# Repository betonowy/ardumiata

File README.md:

# Engine health monitoring for Mazda MX-5 NB1

Firmware for custom Arduino Nano powered device. Mainly for precise engine health monitoring on track days. Features:

- Invisible, non-invasive piggyback off of factory wiring harness if needed at all.
- Modifications are reversible.
- Cleanly integrates with car's interior. 16x2 green display can replace smoking ashtray on NB1. I made a "mounting bracket" for it with a matte painted piece of wood.
- Monitoring engine health and more:
    - (ECT) Coolant temperature - piggybacked and calibrated against factory sensor and ECU measurement circuit. May alternatively use temp gauge circuit, but you're on your own to deal with that.
    - (EOT) Oil temperatoure - from Ecumaster Temperature Sensor.
    - (EOP) Oil pressure - from Ecumaster Pressure Sensor.
    - (BAT) Battery voltage (from ignition).
- Alarm when any measurement exceeds safe limits so you know when to cooldown or make an emergency shutdown.
- If your ECT ever breaks, you will know.

## Important notes

- ECT approximation function might need to be recalibrated/curve fitted for any other car than mine, especially if any part of PCB design is altered. Measuring temperatures/ECT voltage at the back of the engine with device attached and compensating for measured voltages when fan switches on and off at 97C and 93C is good enough, especially if you just need a relative guide for how hot the engine is. If outside EU, check your regional specs specifically.
- Despite the efforts, cabin fan can offset measurements up to 4 degrees upwards when on and it can't be fixed, take that into account or don't turn it.
- ECT relay is required to ensure device does not affect ECU measurements when device is in an inconsistent state i.e. during reset, or engine startup.
- Cars with no AC have a very convenient rubber cap that can feed wires through passenger side firewall.

# Building project

- PCB project initially made in KiCad 8.
- Source compilled with `avr-gcc` toolchain with Arduino package. For guide check out `Arduino-CMake-NG` project. Initially developed on a Linux system.

Assuming basic KiCad and CMake knowledge, you should already know how to build the project.

## Project layout

- `.` - miscelaneous files and root `CMakeLists.txt`.
- `src` - Firmware source code.
- `kicad` - KiCad PCB project.

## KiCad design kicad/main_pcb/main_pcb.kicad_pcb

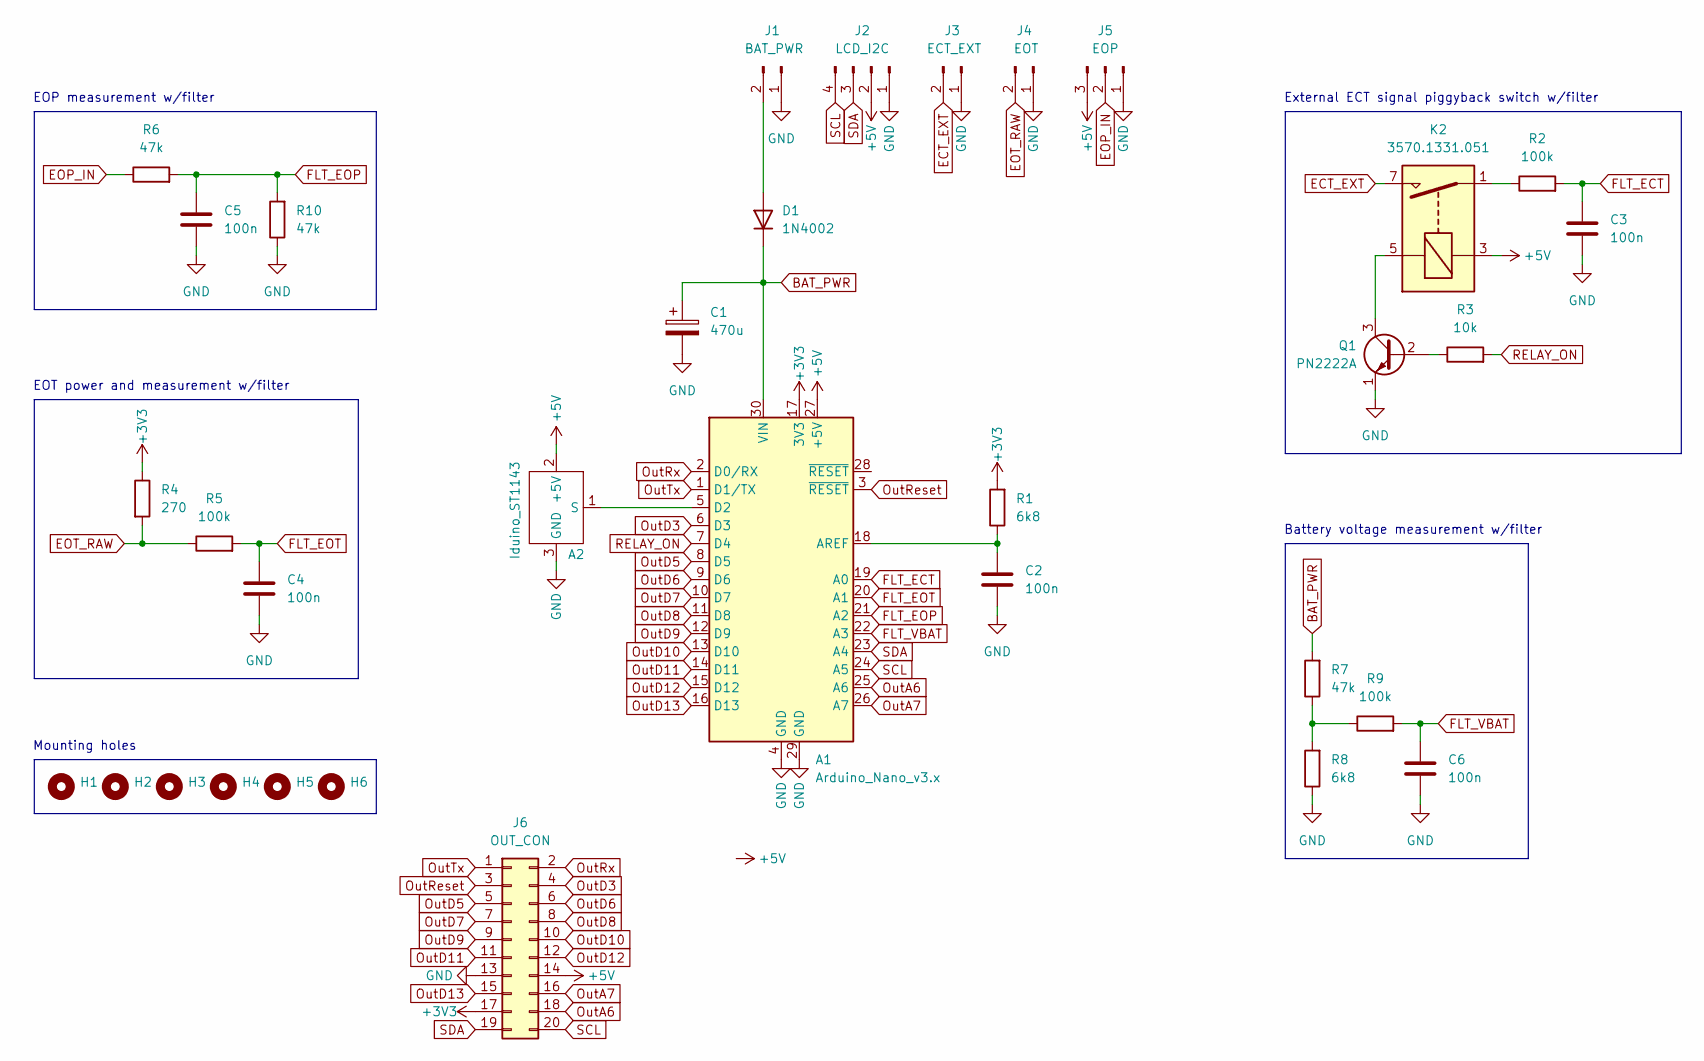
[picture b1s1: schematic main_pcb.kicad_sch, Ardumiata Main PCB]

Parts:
A1: Arduino_Nano_v3.x; Arduino_Nano
A2: Iduino_ST1143
C1: 470u; CP_Radial_D10.0mm_P5.00mm
C2, C3, C4, C5, C6: 100n; C_Disc_D3.8mm_W2.6mm_P2.50mm
D1: 1N4002; D_DO-41_SOD81_P10.16mm_Horizontal
H1, H2, H3, H4, H5, H6: MountingHole_3.5mm
J1: BAT_PWR; Molex_KK-254_AE-6410-02A_1x02_P2.54mm_Vertical
J2: LCD_I2C; Molex_KK-254_AE-6410-04A_1x04_P2.54mm_Vertical
J3: ECT_EXT; Molex_KK-254_AE-6410-02A_1x02_P2.54mm_Vertical
J4: EOT; Molex_KK-254_AE-6410-02A_1x02_P2.54mm_Vertical
J5: EOP; Molex_KK-254_AE-6410-03A_1x03_P2.54mm_Vertical
J6: OUT_CON; IDC-Header_2x10_P2.54mm_Vertical
K2: 3570.1331.051; Relay_SPST_StandexMeder_SIL_Form1A
Q1: PN2222A; TO-92_Inline
R1, R8: 6k8; R_Axial_DIN0207_L6.3mm_D2.5mm_P7.62mm_Horizontal
R2, R5, R9: 100k; R_Axial_DIN0207_L6.3mm_D2.5mm_P7.62mm_Horizontal
R3: 10k; R_Axial_DIN0207_L6.3mm_D2.5mm_P7.62mm_Horizontal
R4: 270; R_Axial_DIN0207_L6.3mm_D2.5mm_P7.62mm_Horizontal
R6, R7, R10: 47k; R_Axial_DIN0207_L6.3mm_D2.5mm_P7.62mm_Horizontal

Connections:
+3V3: A1.17 (3V3), J6.17, R1.2, R4.1
+5V: A1.27 (+5V), A2.2 (+5V), J2.2, J5.3, J6.14, K2.3
BAT_PWR: A1.30 (VIN), C1.1, D1.1 (K), R7.2
ECT_EXT: J3.2, K2.7
EOP_IN: J5.2, R6.1
EOT_RAW: J4.2, R4.2, R5.1
FLT_ECT: A1.19 (A0), C3.1, R2.2
FLT_EOP: A1.21 (A2), C5.1, R6.2, R10.2
FLT_EOT: A1.20 (A1), C4.1, R5.2
FLT_VBAT: A1.22 (A3), C6.1, R9.2
GND: A1.4 (GND), A1.29 (GND), A2.3 (GND), C1.2, C2.2, C3.2, C4.2, C5.2, C6.2, J1.1, J2.1, J3.1, J4.1, J5.1, J6.13, Q1.1 (E), R8.1, R10.1
unnamed: A1.18 (AREF), C2.1, R1.1
unnamed: A1.5 (D2), A2.1 (S)
unnamed: D1.2 (A), J1.2
unnamed: K2.1, R2.1
unnamed: Q1.2 (B), R3.1
unnamed: K2.5, Q1.3 (C)
unnamed: R7.1, R8.2, R9.1
OutA6: A1.25 (A6), J6.18
OutA7: A1.26 (A7), J6.16
OutD3: A1.6 (D3), J6.4
OutD5: A1.8 (D5), J6.5
OutD6: A1.9 (D6), J6.6
OutD7: A1.10 (D7), J6.7
OutD8: A1.11 (D8), J6.8
OutD9: A1.12 (D9), J6.9
OutD10: A1.13 (D10), J6.10
OutD11: A1.14 (D11), J6.11
OutD12: A1.15 (D12), J6.12
OutD13: A1.16 (D13), J6.15
OutReset: A1.3 (~RESET), J6.3
OutRx: A1.2 (D0/RX), J6.2
OutTx: A1.1 (D1/TX), J6.1
RELAY_ON: A1.7 (D4), R3.2
SCL: A1.24 (A5), J2.4, J6.20
SDA: A1.23 (A4), J2.3, J6.19

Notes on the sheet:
EOP measurement w/filter
Battery voltage measurement w/filter
External ECT signal piggyback switch w/filter
Mounting holes
EOT power and measurement w/filter

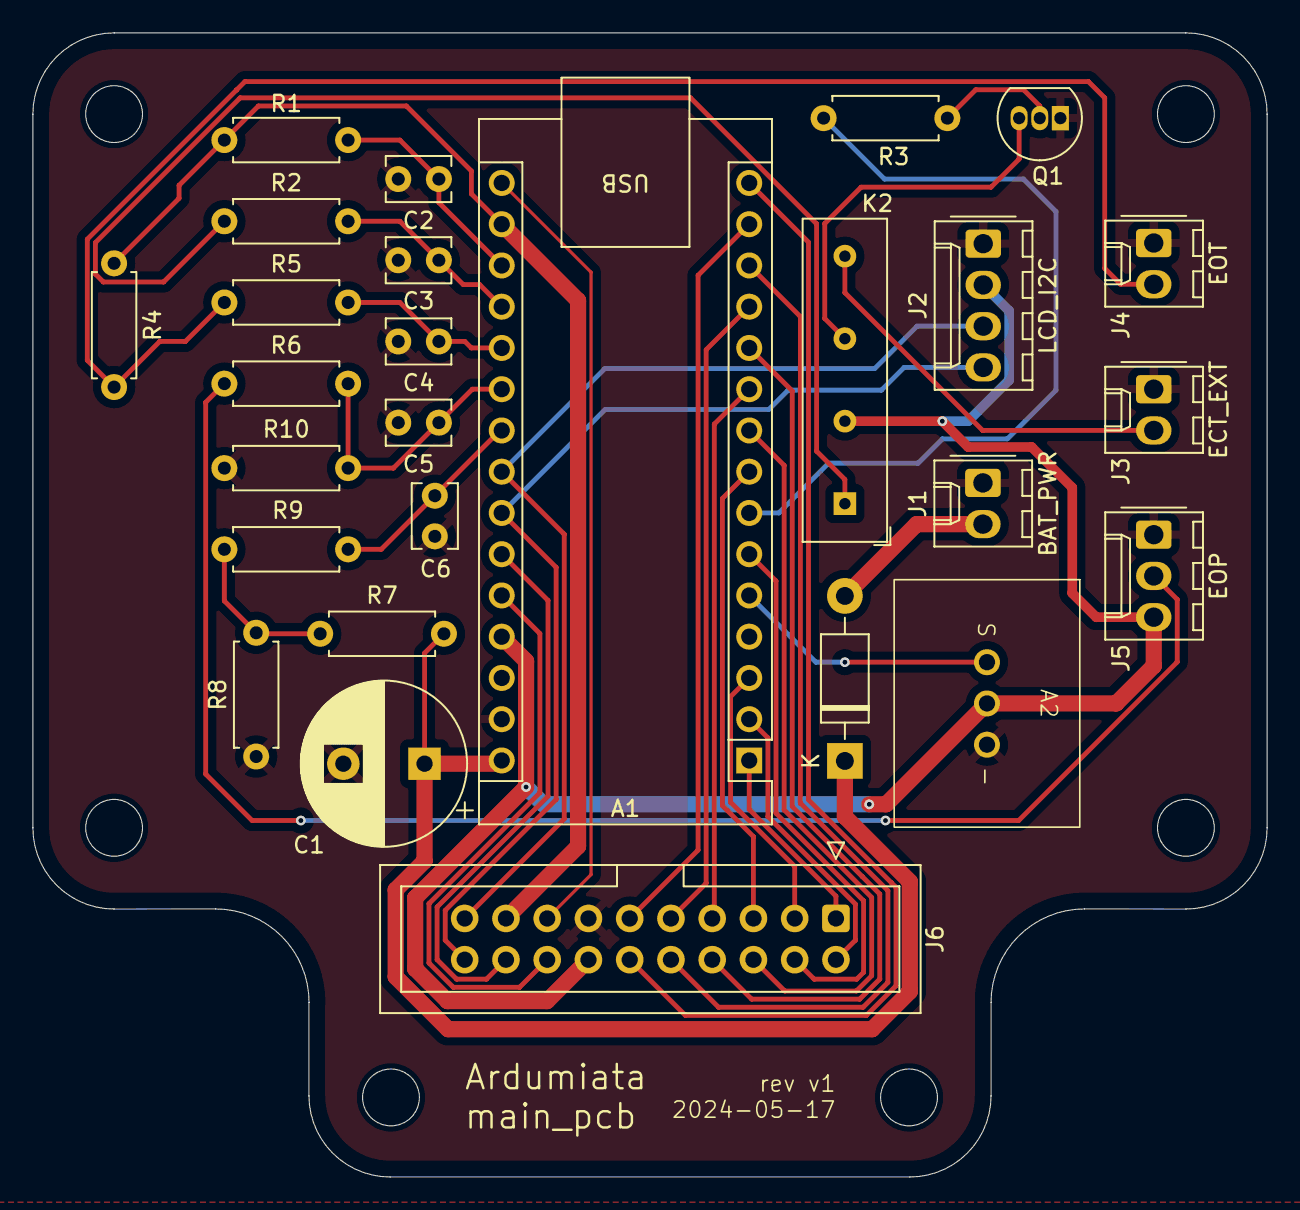
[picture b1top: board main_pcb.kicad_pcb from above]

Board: 2 copper layers, 76.0 x 70.4 mm, 33 parts (0 on the bottom side), 36 nets.

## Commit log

2024-04-27 ECT reading done
2024-04-27 License
2024-05-01 Working prototype
2024-05-01 Battery state and buzzer support
2024-05-02 Refactor and adapt to another LCD, display refinement
2024-05-06 Debug features, sensor test
2024-05-06 Badly calibrated EOT, but it's a start
2024-05-14 Reformat vendored code
2024-05-14 EOT, EOP implementation and calibration
2024-05-14 Add KiCad PCB project
2024-05-14 Pedantic cleanup
2024-05-18 Main PCB final design, refine eot calibration and limits
2024-05-29 Component adjustments and recalibration
2024-06-01 Enable alarms
2024-06-01 Don't trigger oil pressure alarm when the engine is off
2025-04-27 Change high pressure limit to avoid alarms at winter

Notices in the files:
kicad/main_pcb/main_pcb.kicad_pcb:
License: CC BY 4.0
